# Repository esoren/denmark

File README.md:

This code is for an STM32F4-based amplifier controller board. More info is available on my website.

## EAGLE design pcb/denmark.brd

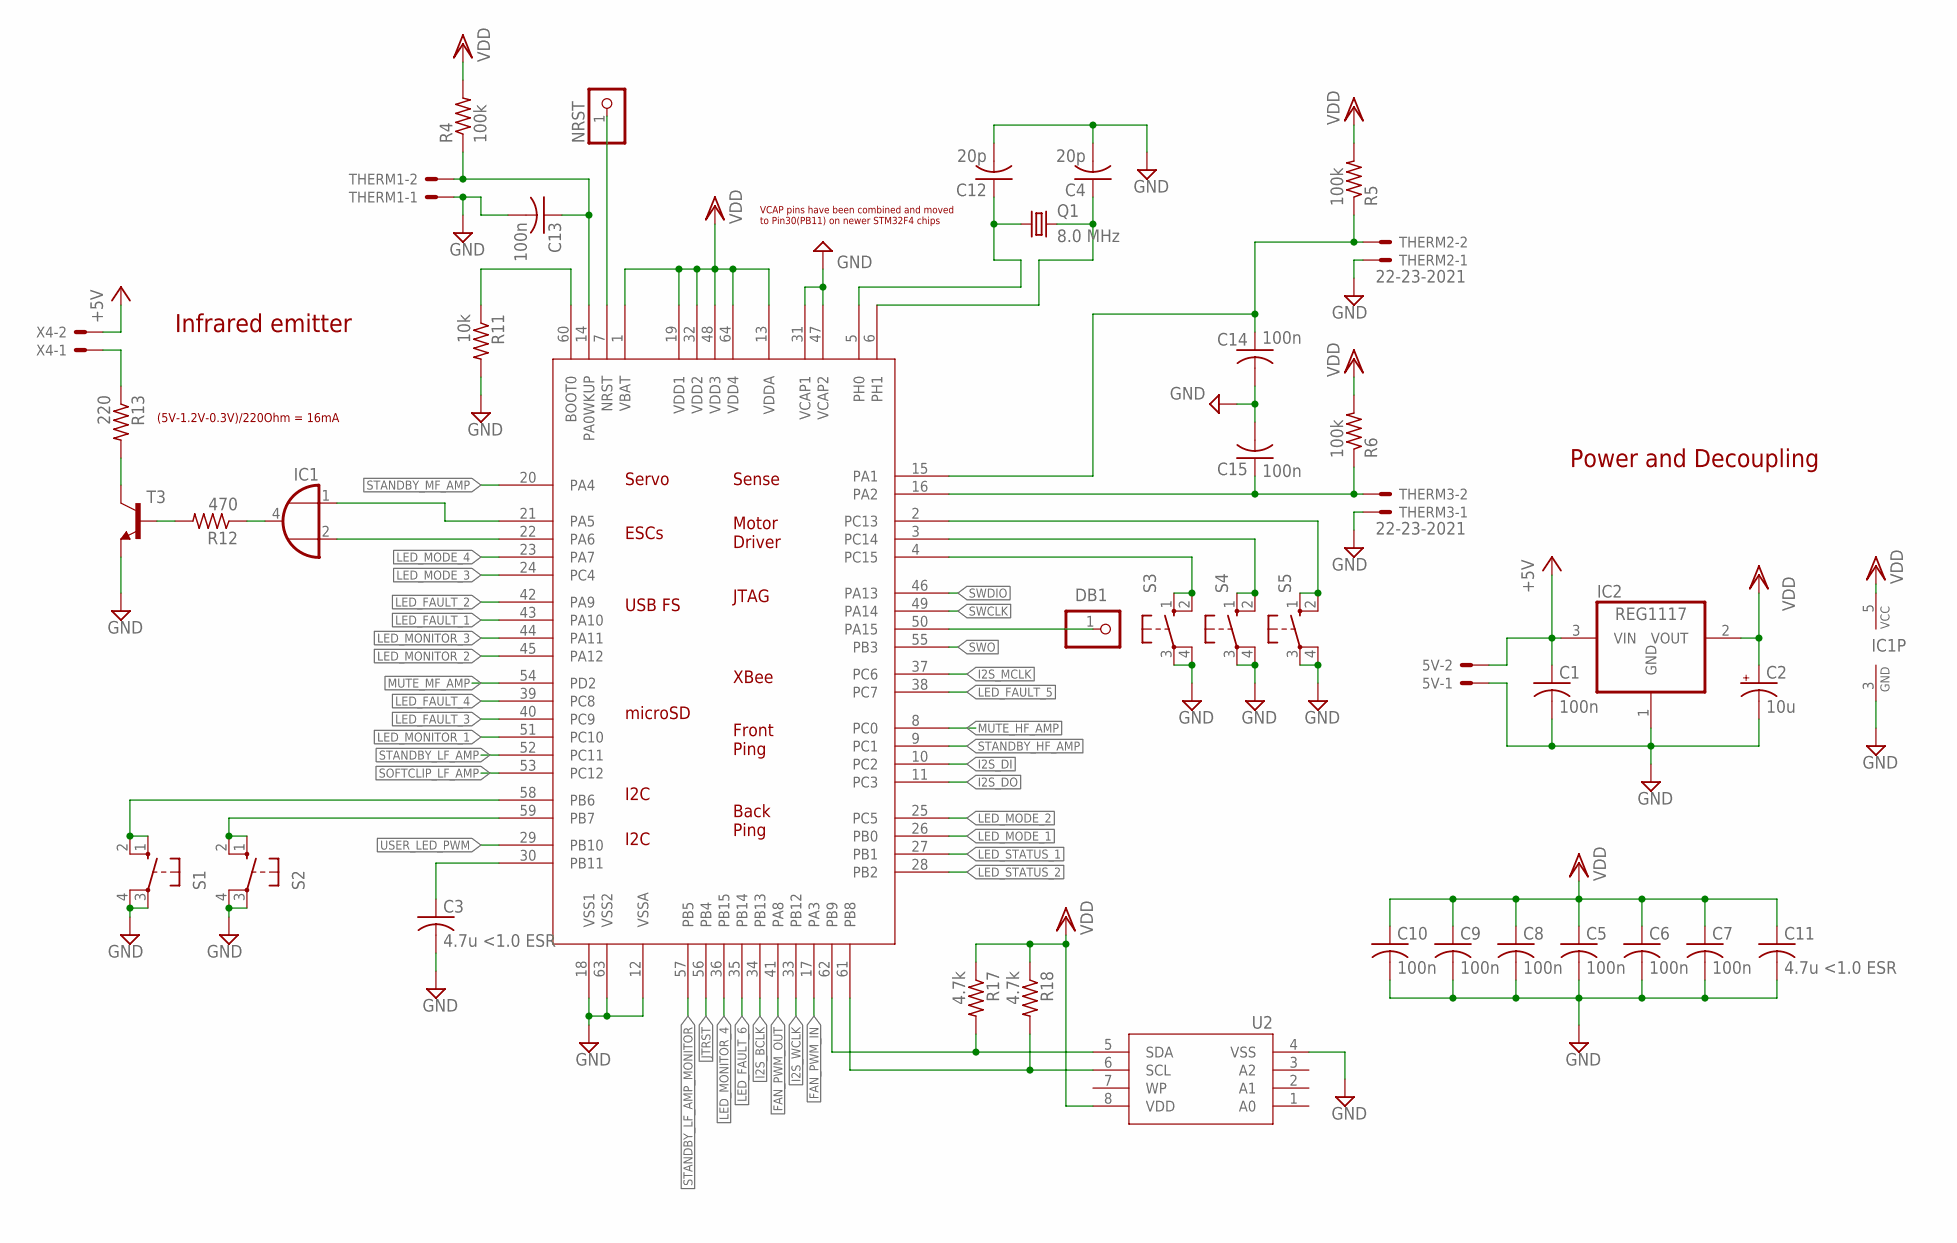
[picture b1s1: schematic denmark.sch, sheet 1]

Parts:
5V: 22-23-2021
C1: 100n; C0805
C2: 10u; E3,5-8
C3, C11: 4.7u <1.0 ESR; C1206
C4, C12: 20p; C0603K
C5, C6, C7, C8, C9, C10, C13, C14, C15: 100n; C0603K
DB1: PINHD-1X1; 1X01
IC1: 74AHC1G32DBV; SOT23-5
IC2: REG1117; SOT223
NRST: PINHD-1X1; 1X01
Q1: 8.0 MHz; HC49U-V
R4, R5, R6: 100k; R0603
R11: 10k; R0603
R12: 470; R0603
R13: 220; R0603
R17, R18: 4.7k; R0603
S1, S2, S3, S4, S5: 10-XX; B3F-10XX
T3: MMBT3904LT1-NPN-SOT23-BEC; SOT23-BEC
THERM1, THERM2, THERM3: 22-23-2021
U1: STM32F4_10X10_LQFP64; LQFP-ST-64-2
U2: MB85RCSOIC8; SOIC8
X4: 22-23-2021

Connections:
+5V: 5V.2, C1.1, IC2.3 (VIN), X4.2; also elsewhere on the board
BUTTON1_INPUT: S1.1 (S), S1.2 (S1), U1.58 (PB6)
BUTTON2_INPUT: S2.1 (S), S2.2 (S1), U1.59 (PB7)
BUTTON3_INPUT: S3.1 (S), S3.2 (S1), U1.4 (PC15)
BUTTON4_INPUT: S4.1 (S), S4.2 (S1), U1.3 (PC14)
BUTTON5_INPUT: S5.1 (S), S5.2 (S1), U1.2 (PC13)
FAN_PWM_IN: U1.17 (PA3); also elsewhere on the board
FAN_PWM_OUT: U1.41 (PA8); also elsewhere on the board
GND: 5V.1, C1.2, C2.-, C3.2, C4.2, C5.2, C6.2, C7.2, C8.2, C9.2, C10.2, C11.2, C12.2, C13.2, C14.2, C15.2, IC1.3 (GND), IC2.1 (GND), R11.2, S1.3, S1.4 (P1), S2.3, S2.4 (P1), S3.3, S3.4 (P1), S4.3, S4.4 (P1), S5.3, S5.4 (P1), T3.E, THERM1.1, THERM2.1, THERM3.1, U1.12 (VSSA), U1.18 (VSS1), U1.31 (VCAP1), U1.47 (VCAP2), U1.63 (VSS2), U2.4 (VSS); also elsewhere on the board
I2C_SCL: R18.2, U1.61 (PB8), U2.6 (SCL)
I2C_SDA: R17.2, U1.62 (PB9), U2.5 (SDA)
I2S_BCLK: U1.34 (PB13); also elsewhere on the board
I2S_DI: U1.10 (PC2); also elsewhere on the board
I2S_DO: U1.11 (PC3); also elsewhere on the board
I2S_MCLK: U1.37 (PC6); also elsewhere on the board
I2S_WCLK: U1.33 (PB12); also elsewhere on the board
IR_BASE: R12.2, T3.B
IR_CARRIER_OUT: IC1.2 (I1), U1.22 (PA6)
IR_COLLECTOR: R13.2, T3.C
IR_SIGNAL_OUT: IC1.1 (I0), U1.21 (PA5)
JTRST: U1.56 (PB4); also elsewhere on the board
LED_FAULT_1: U1.43 (PA10); also elsewhere on the board
LED_FAULT_2: U1.42 (PA9); also elsewhere on the board
LED_FAULT_3: U1.40 (PC9); also elsewhere on the board
LED_FAULT_4: U1.39 (PC8); also elsewhere on the board
LED_FAULT_5: U1.38 (PC7); also elsewhere on the board
LED_FAULT_6: U1.35 (PB14); also elsewhere on the board
LED_MODE_1: U1.26 (PB0); also elsewhere on the board
LED_MODE_2: U1.25 (PC5); also elsewhere on the board
LED_MODE_3: U1.24 (PC4); also elsewhere on the board
LED_MODE_4: U1.23 (PA7); also elsewhere on the board
LED_MONITOR_1: U1.51 (PC10); also elsewhere on the board
LED_MONITOR_2: U1.45 (PA12); also elsewhere on the board
LED_MONITOR_3: U1.44 (PA11); also elsewhere on the board
LED_MONITOR_4: U1.36 (PB15); also elsewhere on the board
LED_STATUS_1: U1.27 (PB1); also elsewhere on the board
LED_STATUS_2: U1.28 (PB2); also elsewhere on the board
MUTE_HF_AMP: U1.8 (PC0); also elsewhere on the board
MUTE_MF_AMP: U1.54 (PD2); also elsewhere on the board
unnamed: C3.1, U1.30 (PB11)
unnamed: DB1.1, U1.50 (PA15)
unnamed: R11.1, U1.60 (BOOT0)
unnamed: NRST.1, U1.7 (NRST)
unnamed: IC1.4 (O), R12.1
unnamed: R13.1, X4.1
RCC_OSC_IN: C12.1, Q1.1, U1.5 (PH0)
RCC_OSC_OUT: C4.1, Q1.2, U1.6 (PH1)
SOFTCLIP_LF_AMP: U1.53 (PC12); also elsewhere on the board
STANDBY_HF_AMP: U1.9 (PC1); also elsewhere on the board
STANDBY_LF_AMP: U1.52 (PC11); also elsewhere on the board
STANDBY_LF_AMP_MONITOR: U1.57 (PB5); also elsewhere on the board
STANDBY_MF_AMP: U1.20 (PA4); also elsewhere on the board
SWCLK: U1.49 (PA14); also elsewhere on the board
SWDIO: U1.46 (PA13); also elsewhere on the board
SWO: U1.55 (PB3); also elsewhere on the board
THERM1_ANALOG_INPUT: C13.1, R4.1, THERM1.2, U1.14 (PA0WKUP)
THERM2_ANALOG_INPUT: C14.1, R5.1, THERM2.2, U1.15 (PA1)
THERM3_ANALOG_INPUT: C15.1, R6.1, THERM3.2, U1.16 (PA2)
USER_LED_PWM: U1.29 (PB10); also elsewhere on the board
VDD: C2.+, C5.1, C6.1, C7.1, C8.1, C9.1, C10.1, C11.1, IC1.5 (VCC), IC2.2 (VOUT), R4.2, R5.2, R6.2, R17.1, R18.1, U1.1 (VBAT), U1.13 (VDDA), U1.19 (VDD1), U1.32 (VDD2), U1.48 (VDD3), U1.64 (VDD4), U2.8 (VDD); also elsewhere on the board

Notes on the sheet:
Power and Decoupling
(5V-1.2V-0.3V)/220Ohm = 16mA
Infrared emitter
VCAP pins have been combined and moved to Pin30(PB11) on newer STM32F4 chips

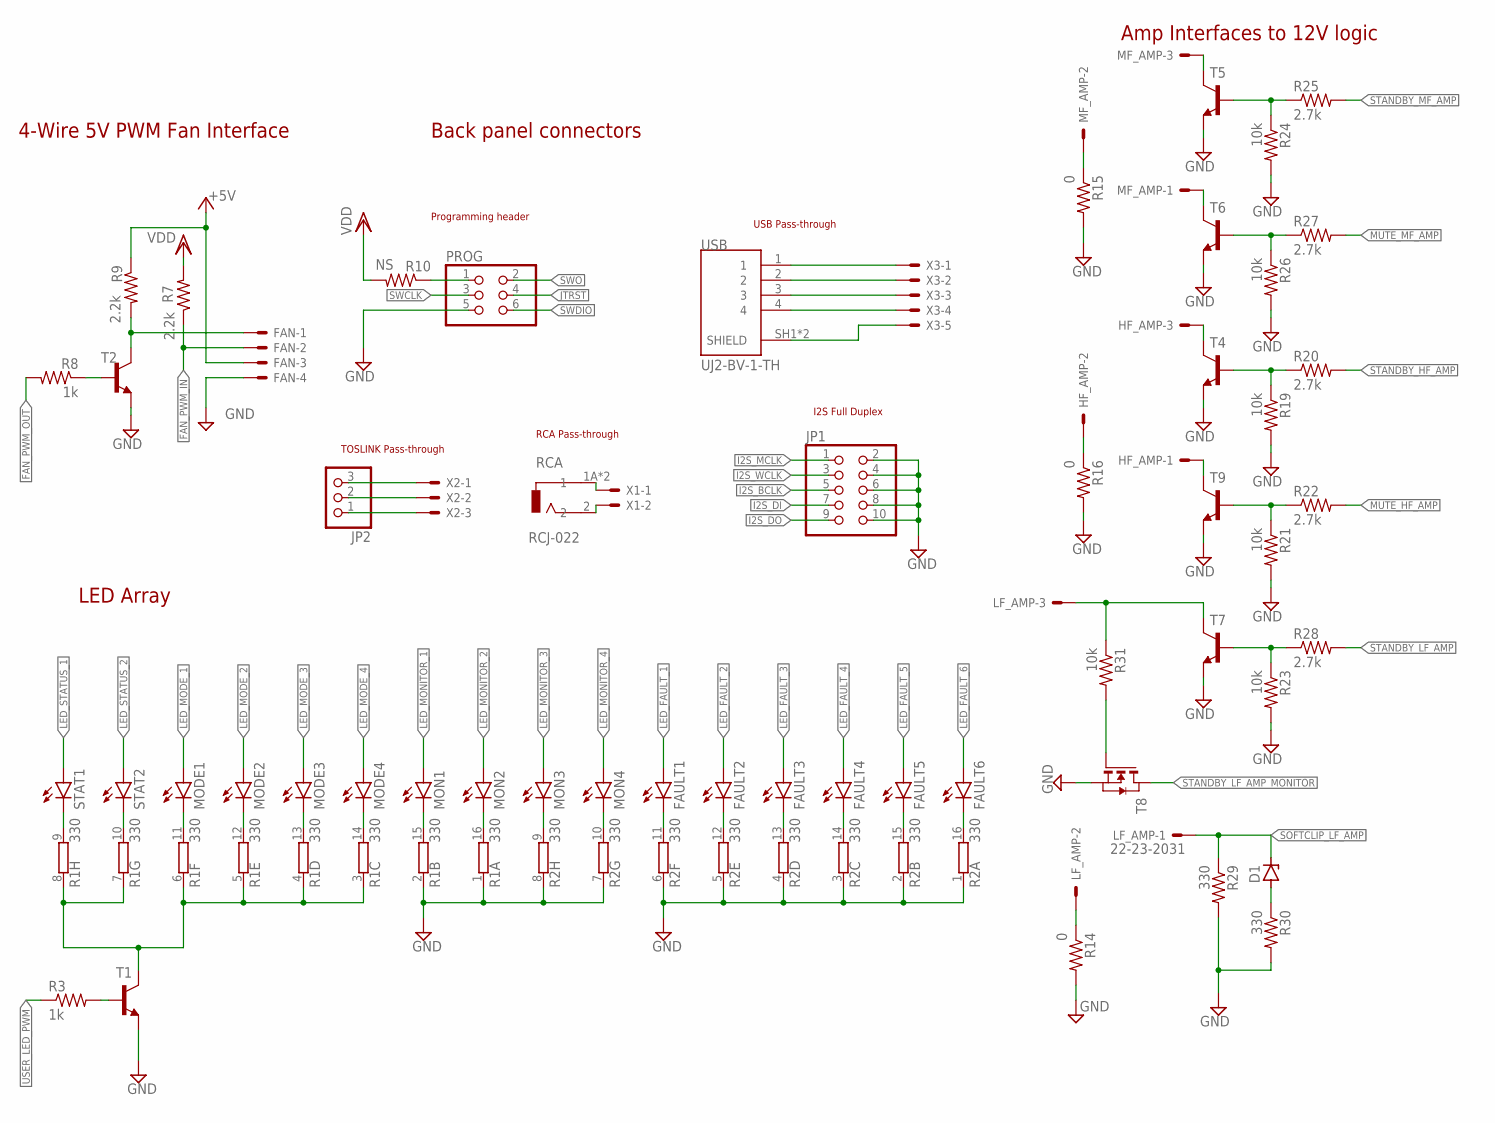
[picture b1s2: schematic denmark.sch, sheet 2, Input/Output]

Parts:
D1: ZENER-DIODESOD80C; SOD80C
FAN: 22-23-2041
FAULT1, FAULT2, FAULT3, FAULT4, FAULT5, FAULT6: LEDCHIPLED_0805; CHIPLED_0805
HF_AMP: 22-23-2031
JP1: PINHD-2X5; 2X05
JP2: PINHD-1X3; 1X03
LF_AMP: 22-23-2031
MF_AMP: 22-23-2031
MODE1, MODE2, MODE3, MODE4: LEDCHIPLED_0805; CHIPLED_0805
MON1, MON2, MON3, MON4: LEDCHIPLED_0805; CHIPLED_0805
PROG: PINHD-2X3; 2X03
R1, R2: 330; SO16
R3, R8: 1k; R0603
R7, R9: 2.2k; R0603
R10: NS; R0603
R14, R15, R16: 0; R0603
R19, R21, R23, R24, R26, R31: 10k; R0603
R20, R22, R25, R27, R28: 2.7k; R0603
R29, R30: 330; R0603
RCA: RCJ-022; CUI_RCJ-022
STAT1, STAT2: LEDCHIPLED_0805; CHIPLED_0805
T1, T2, T4, T5, T6, T7, T9: MMBT3904LT1-NPN-SOT23-BEC; SOT23-BEC
T8: NMOSSOT23; SOT-23
USB: UJ2-BV-1-TH; CUI_UJ2-BV-1-TH
X1: 22-23-2021
X2: 22-23-2031
X3: 22-23-2051

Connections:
+5V: FAN.3, R9.1; also elsewhere on the board
FAN_PWM_IN: FAN.2, R7.1; also elsewhere on the board
FAN_PWM_OUT: R8.2; also elsewhere on the board
GND: FAN.4, JP1.2, JP1.4, JP1.6, JP1.8, JP1.10, PROG.5, R1.1, R1.2 (1), R2.1, R2.2 (1), R2.3 (1), R2.4 (1), R2.5 (1), R2.6 (1), R2.7 (1), R2.8 (1), R14.2, R15.2, R16.2, R19.2, R21.2, R23.2, R24.2, R26.2, R29.2, R30.2, T1.E, T2.E, T4.E, T5.E, T6.E, T7.E, T8.2 (S), T9.E; also elsewhere on the board
I2S_BCLK: JP1.5; also elsewhere on the board
I2S_DI: JP1.7; also elsewhere on the board
I2S_DO: JP1.9; also elsewhere on the board
I2S_MCLK: JP1.1; also elsewhere on the board
I2S_WCLK: JP1.3; also elsewhere on the board
JTRST: PROG.4; also elsewhere on the board
LED_FAULT_1: FAULT1.A; also elsewhere on the board
LED_FAULT_2: FAULT2.A; also elsewhere on the board
LED_FAULT_3: FAULT3.A; also elsewhere on the board
LED_FAULT_4: FAULT4.A; also elsewhere on the board
LED_FAULT_5: FAULT5.A; also elsewhere on the board
LED_FAULT_6: FAULT6.A; also elsewhere on the board
LED_MODE_1: MODE1.A; also elsewhere on the board
LED_MODE_2: MODE2.A; also elsewhere on the board
LED_MODE_3: MODE3.A; also elsewhere on the board
LED_MODE_4: MODE4.A; also elsewhere on the board
LED_MONITOR_1: MON1.A; also elsewhere on the board
LED_MONITOR_2: MON2.A; also elsewhere on the board
LED_MONITOR_3: MON3.A; also elsewhere on the board
LED_MONITOR_4: MON4.A; also elsewhere on the board
LED_STATUS_1: STAT1.A; also elsewhere on the board
LED_STATUS_2: STAT2.A; also elsewhere on the board
LED_USER_ANODE: R1.3 (1), R1.4 (1), R1.5 (1), R1.6 (1), R1.7 (1), R1.8 (1), T1.C
MUTE_HF_AMP: R22.2; also elsewhere on the board
MUTE_MF_AMP: R27.2; also elsewhere on the board
unnamed: R1.9 (2), STAT1.C
unnamed: R1.10 (2), STAT2.C
unnamed: MODE1.C, R1.11 (2)
unnamed: MODE2.C, R1.12 (2)
unnamed: MODE3.C, R1.13 (2)
unnamed: MODE4.C, R1.14 (2)
unnamed: MON1.C, R1.15 (2)
unnamed: MON2.C, R1.16 (2)
unnamed: MON3.C, R2.9 (2)
unnamed: MON4.C, R2.10 (2)
unnamed: FAULT1.C, R2.11 (2)
unnamed: FAULT2.C, R2.12 (2)
unnamed: FAULT3.C, R2.13 (2)
unnamed: FAULT4.C, R2.14 (2)
unnamed: FAULT5.C, R2.15 (2)
unnamed: FAULT6.C, R2.16 (2)
unnamed: R3.2, T1.B
unnamed: HF_AMP.3, T4.C
unnamed: R19.1, R20.1, T4.B
unnamed: HF_AMP.1, T9.C
unnamed: R21.1, R22.1, T9.B
unnamed: LF_AMP.3, R31.1, T7.C
unnamed: MF_AMP.3, T5.C
unnamed: R24.1, R25.1, T5.B
unnamed: FAN.1, R9.2, T2.C
unnamed: R8.1, T2.B
unnamed: MF_AMP.1, T6.C
unnamed: R26.1, R27.1, T6.B
unnamed: R23.1, R28.1, T7.B
unnamed: RCA.1A (1), RCA.1B (1), X1.1
unnamed: RCA.2, X1.2
unnamed: JP2.3, X2.1
unnamed: JP2.2, X2.2
unnamed: JP2.1, X2.3
unnamed: R31.2, T8.3 (G)
unnamed: USB.1, X3.1
unnamed: USB.2, X3.2
unnamed: USB.3, X3.3
unnamed: USB.4, X3.4
unnamed: USB.SH1 (SHIELD), USB.SH2 (SHIELD), X3.5
unnamed: D1.A, R30.1
unnamed: LF_AMP.2, R14.1
unnamed: MF_AMP.2, R15.1
unnamed: HF_AMP.2, R16.1
SOFTCLIP_LF_AMP: D1.C, LF_AMP.1, R29.1; also elsewhere on the board
STANDBY_HF_AMP: R20.2; also elsewhere on the board
STANDBY_LF_AMP: R28.2; also elsewhere on the board
STANDBY_LF_AMP_MONITOR: T8.1 (D); also elsewhere on the board
STANDBY_MF_AMP: R25.2; also elsewhere on the board
ST_VDD: PROG.1, R10.1
SWCLK: PROG.3; also elsewhere on the board
SWDIO: PROG.6; also elsewhere on the board
SWO: PROG.2; also elsewhere on the board
USER_LED_PWM: R3.1; also elsewhere on the board
VDD: R7.2, R10.2; also elsewhere on the board

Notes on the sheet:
Back panel connectors
LED Array
TOSLINK Pass-through
I2S Full Duplex
USB Pass-through
Programming header
RCA Pass-through
Amp Interfaces to 12V logic
4-Wire 5V PWM Fan Interface

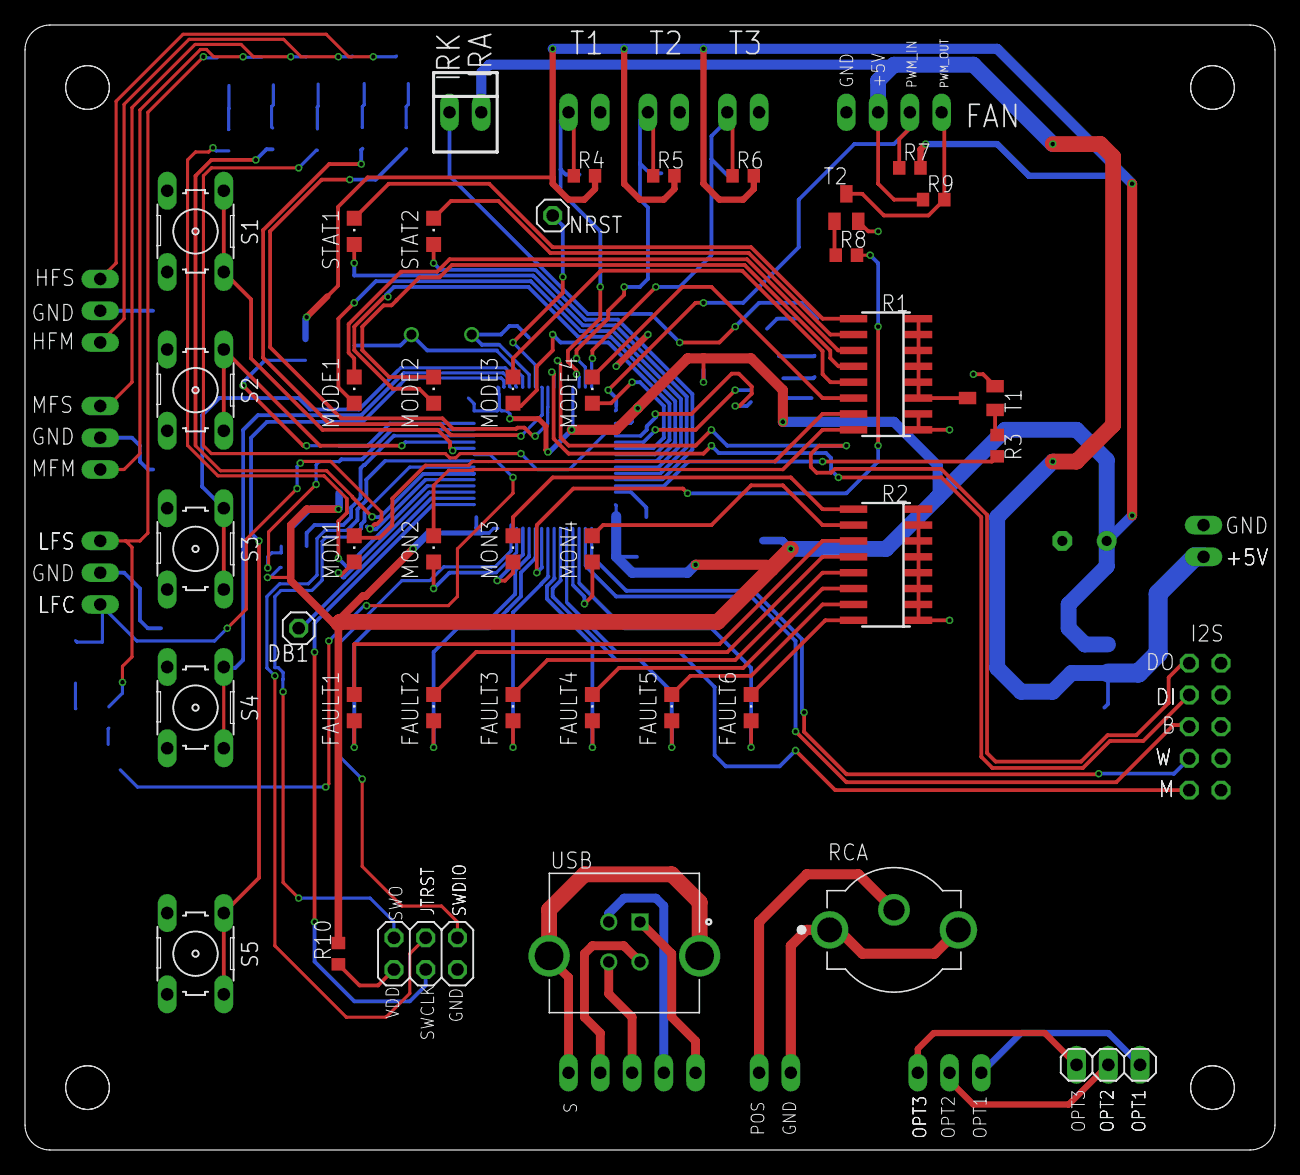
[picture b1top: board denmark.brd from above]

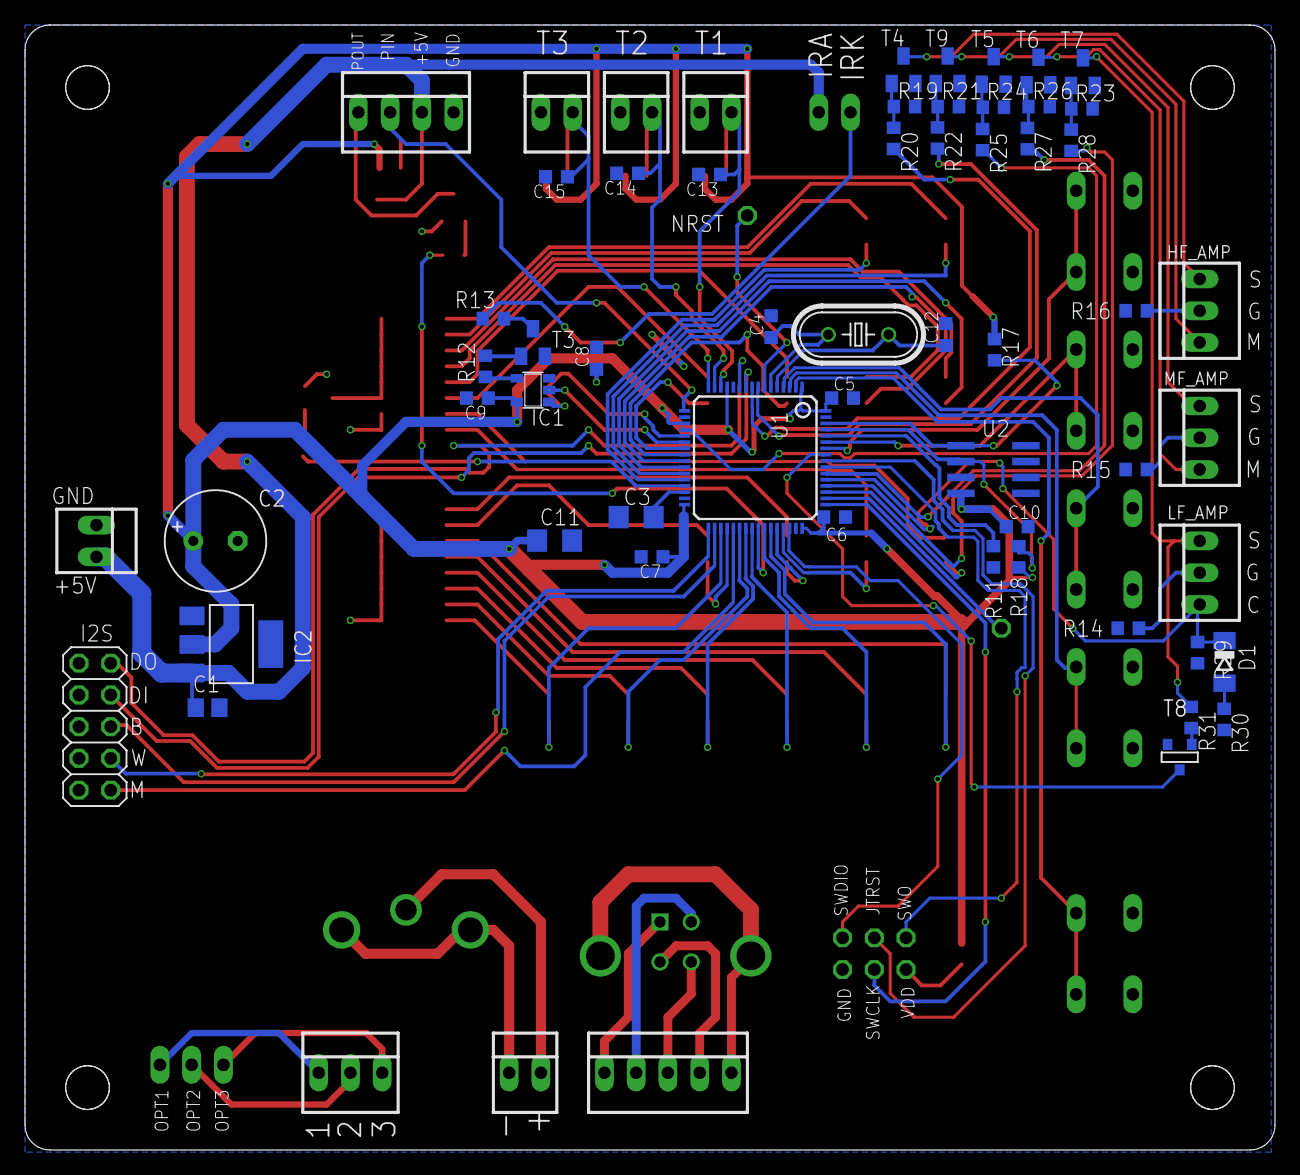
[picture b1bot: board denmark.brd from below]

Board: 2 copper layers, 100.0 x 90.0 mm, 101 parts (61 on the bottom side), 106 nets.

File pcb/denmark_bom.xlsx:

Digikey P/N | QTY | Reference | Doubled | Description
399-C0603C104K8RAC7867CT-ND | 10 | C1 C5 C6 C7 C8 C9 C10 C13 C14 C15 | 20 | 100nf 0603 capacitor
587-GMK316AB7475MLHTCT-ND | 2 | C3 C11 | 4 | 4.7uF 1206 low ESR
1189-1513-1-ND | 1 | C2 | 2 | 10uF 8mm cap
475-1410-1-ND | 6 | MODE1 MODE2 MODE3 MODE4 STAT1 STAT2 | 12 | green 0805 led
732-4987-1-ND | 4 | MON1 MON2 MON3 MON4 | 8 | yellow 0805 led
475-1278-1-ND | 6 | FAULT1 FAULT2 FAULT3 FAULT4 FAULT5 FAULT6 | 12 | red 0805 led
497-STM32F401RET7-ND | 1 | U1 | 2 | stm32f4 mcu
RNCP0603FTD1K00CT-ND | 4 | R3 R8 | 8 | 1k 0603 resistor
311-100KHRCT-ND | 3 | R4 R5 R6 | 6 | 100k 0603 resistor
311-2.20KHRCT-ND | 2 | R7 R9 | 4 | 2.2k 0603 resistor
RMCF0201FT10K0CT-ND | 7 | R11 R19 R21 R23 R24 R26 R31 | 14 | 10k 0603 resistor
311-4.7KGRCT-ND | 2 | R17 R18 | 4 | 4.7k 0603 resistor
RMCF0603ZT0R00CT-ND | 3 | R14 R15 R16 | 6 | 0 0603 resistor
VSSR16-330-JI-ND | 2 | R1 R2 | 4 | resistor network - 330
865-1261-1-ND | 1 | U2 | 2 | FRAM
497-1242-1-ND | 1 | IC2 | 2 | 1117 LDO
XC1922-ND | 1 | Q1 | 2 | 8.0 MHz Crystal
CP-1408-ND | 1 | RCA | 2 | RCA connector
102-4000-ND | 1 | USB | 2 | USB connector
296-SN74AHC1G08DBV3CT-ND | 1 | IC1 | 2 | AND Gate
SW400-ND | 5 | S1 S2 S3 S4 S5 | 10 | tactile switch
A98333-ND | 6 | 5V THERM1 THERM2 THERM3 X1 X4 | 12 | 2 pin terminal block 0.1"
A98334-ND | 4 | X2 LF_AMP MF_AMP HF_AMP | 8 | 3 pin terminal block 0.1":
A98335-ND | 1 | FAN | 2 | 4 pin terminal block 0.1"
A98336-ND | 1 | X3 | 2 | 5 pin terminal block 0.1"
MMBT3904LT1HTSA1CT-ND | 7 | T1 T2 T3 T5 T6 T7 T9 | 14 | npn transistor sot23
1276-1187-1-ND | 2 | C4 C12 | 4 | 20p 0603 capacitor
CR0603-JW-331ELFCT-ND | 2 | R29 R30 | 4 | 330 0603 resistor
118-CR0603-JW-221ELFCT-ND | 1 | R12 | 2 | 220 0603 resistor
CR0603-JW-471ELFCT-ND | 1 | R13 | 2 | 470 0603 resistor
2N7002-FDICT-ND | 1 | T8 | 2 | NMOS switch
1727-2097-1-ND | 1 | D1 | 2 | 3v3 zener diode

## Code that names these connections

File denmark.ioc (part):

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Mcu.Name=STM32F401R(D-E)Tx
Mcu.Package=LQFP64
Mcu.UserName=STM32F401RETx
PA0-WKUP.GPIOParameters=GPIO_Label
PA0-WKUP.GPIO_Label=THERM1_ANALOG_INPUT
PA0-WKUP.Signal=ADCx_IN0
PA1.GPIOParameters=GPIO_Label
PA1.GPIO_Label=THERM2_ANALOG_INPUT
PA1.Signal=ADCx_IN1
PA10.GPIOParameters=GPIO_Label
PA10.GPIO_Label=LED_FAULT_1
PA10.Signal=GPIO_Output
PA11.GPIOParameters=GPIO_Label
PA11.GPIO_Label=LED_MONITOR_3
PA11.Signal=GPIO_Output
PA12.GPIOParameters=GPIO_Label
PA12.GPIO_Label=LED_MONITOR_2
PA12.Signal=GPIO_Output
PA13.Mode=JTAG_5_pins
PA13.Signal=SYS_JTMS-SWDIO
PA14.Mode=JTAG_5_pins
PA14.Signal=SYS_JTCK-SWCLK
PA15.Mode=JTAG_5_pins
PA15.Signal=SYS_JTDI
PA2.GPIOParameters=GPIO_Label
PA2.GPIO_Label=THERM3_ANALOG_INPUT
PA2.Signal=ADCx_IN2
PA3.Signal=S_TIM5_CH4
PA4.GPIOParameters=PinState,GPIO_Label
PA4.GPIO_Label=STANDBY_MF_AMP
PA4.PinState=GPIO_PIN_SET
PA4.Signal=GPIO_Output
PA5.GPIOParameters=GPIO_Label
PA5.GPIO_Label=IR_SIGNAL_OUT
PA5.Signal=GPIO_Output
PA6.GPIOParameters=GPIO_Label
PA6.GPIO_Label=IR_CARRIER_OUT
PA6.Signal=S_TIM3_CH1
PA7.GPIOParameters=GPIO_Label
PA7.GPIO_Label=LED_MODE_4
PA7.Signal=GPIO_Output
PA8.GPIOParameters=GPIO_Speed,GPIO_Label
PA8.GPIO_Label=FAN_PWM
PA8.GPIO_Speed=GPIO_SPEED_FREQ_HIGH
PA8.Signal=S_TIM1_CH1
PA9.GPIOParameters=GPIO_Label
PA9.GPIO_Label=LED_FAULT_2
PA9.Signal=GPIO_Output
PB0.GPIOParameters=GPIO_Label
PB0.GPIO_Label=LED_MODE_1
PB0.Signal=GPIO_Output
PB1.GPIOParameters=GPIO_Label
PB1.GPIO_Label=LED_STATUS_1
PB1.Signal=GPIO_Output
PB10.GPIOParameters=GPIO_Label
PB10.GPIO_Label=USER_LED_PWM
PB10.Signal=S_TIM2_CH3
PB14.GPIOParameters=GPIO_Label
PB14.GPIO_Label=LED_FAULT_6
PB14.Signal=GPIO_Output
PB15.GPIOParameters=GPIO_Label
PB15.GPIO_Label=LED_MONITOR_4
PB15.Signal=GPIO_Output
PB2.GPIOParameters=GPIO_Label
PB2.GPIO_Label=LED_STATUS_2
PB2.Signal=GPIO_Output
PB3.Mode=JTAG_5_pins
PB3.Signal=SYS_JTDO-SWO
PB4.Mode=JTAG_5_pins
PB4.Signal=SYS_JTRST
PB6.GPIOParameters=GPIO_PuPd,GPIO_Label
PB6.GPIO_Label=BUTTON1_INPUT
PB6.GPIO_PuPd=GPIO_PULLUP
PB6.Signal=GPIO_Input
PB7.GPIOParameters=GPIO_PuPd,GPIO_Label
PB7.GPIO_Label=BUTTON2_INPUT
PB7.GPIO_PuPd=GPIO_PULLUP
PB7.Signal=GPIO_Input
PB8.GPIOParameters=GPIO_Label
PB8.GPIO_Label=I2C_SCL
PB8.Mode=I2C
PB8.Signal=I2C1_SCL
PB9.GPIOParameters=GPIO_Label
PB9.GPIO_Label=I2C_SDA
PB9.Mode=I2C
PB9.Signal=I2C1_SDA
PC0.GPIOParameters=PinState,GPIO_Label
PC0.GPIO_Label=MUTE_HF_AMP
PC0.PinState=GPIO_PIN_SET
PC0.Signal=GPIO_Output
PC1.GPIOParameters=PinState,GPIO_Label
PC1.GPIO_Label=STANDBY_HF_AMP
PC1.PinState=GPIO_PIN_SET
PC1.Signal=GPIO_Output
PC10.GPIOParameters=GPIO_Label
PC10.GPIO_Label=LED_MONITOR_1
PC10.Signal=GPIO_Output
PC11.GPIOParameters=PinState,GPIO_PuPd,GPIO_Label,GPIO_ModeDefaultOutputPP
PC11.GPIO_Label=STANDBY_LF_AMP_OUTPUT
PC11.GPIO_ModeDefaultOutputPP=GPIO_MODE_OUTPUT_PP
PC11.GPIO_PuPd=GPIO_NOPULL
PC11.PinState=GPIO_PIN_SET
PC11.Signal=GPIO_Output
PC12.GPIOParameters=GPIO_PuPd,GPIO_Label
PC12.GPIO_Label=SOFTCLIP_LF_AMP_INPUT
PC12.GPIO_PuPd=GPIO_PULLUP
PC12.Signal=GPIO_Input
PC13-ANTI_TAMP.GPIOParameters=GPIO_PuPd,GPIO_Label
PC13-ANTI_TAMP.GPIO_Label=BUTTON5_INPUT
PC13-ANTI_TAMP.GPIO_PuPd=GPIO_PULLUP
PC13-ANTI_TAMP.Signal=GPIO_Input
PC14-OSC32_IN.GPIOParameters=GPIO_PuPd,GPIO_Label
PC14-OSC32_IN.GPIO_Label=BUTTON4_INPUT
PC14-OSC32_IN.GPIO_PuPd=GPIO_PULLUP
PC14-OSC32_IN.Signal=GPIO_Input
PC15-OSC32_OUT.GPIOParameters=GPIO_PuPd,GPIO_Label
PC15-OSC32_OUT.GPIO_Label=BUTTON3_INPUT
PC15-OSC32_OUT.GPIO_PuPd=GPIO_PULLUP
PC15-OSC32_OUT.Signal=GPIO_Input
PC3.GPIOParameters=GPIO_PuPd,GPIO_Label
PC3.GPIO_Label=STANDBY_PROTECT_LF_INPUT
PC3.GPIO_PuPd=GPIO_PULLUP
PC3.Signal=GPIO_Input
PC4.GPIOParameters=GPIO_Label
PC4.GPIO_Label=LED_MODE_3
PC4.Signal=GPIO_Output
PC5.GPIOParameters=GPIO_Label
PC5.GPIO_Label=LED_MODE_2
PC5.Signal=GPIO_Output
PC6.GPIOParameters=GPIO_PuPd,GPIO_Label
PC6.GPIO_Label=GENERAL_INPUT_1
PC6.GPIO_PuPd=GPIO_PULLUP
PC6.Signal=GPIO_Input
PC7.GPIOParameters=GPIO_Label
PC7.GPIO_Label=LED_FAULT_5
PC7.Signal=GPIO_Output
PC8.GPIOParameters=GPIO_Label
PC8.GPIO_Label=LED_FAULT_4
PC8.Signal=GPIO_Output
PC9.GPIOParameters=GPIO_Label
PC9.GPIO_Label=LED_FAULT_3
PC9.Signal=GPIO_Output
PD2.GPIOParameters=PinState,GPIO_Label
PD2.GPIO_Label=MUTE_MF_AMP
PD2.PinState=GPIO_PIN_SET
PD2.Signal=GPIO_Output
PH0\ -\ OSC_IN.Mode=HSE-External-Oscillator
PH0\ -\ OSC_IN.Signal=RCC_OSC_IN
PH1\ -\ OSC_OUT.Mode=HSE-External-Oscillator
PH1\ -\ OSC_OUT.Signal=RCC_OSC_OUT
RCC.HSE_VALUE=8000000
RCC.SYSCLKFreq_VALUE=84000000
RCC.SYSCLKSource=RCC_SYSCLKSOURCE_PLLCLK
board=custom

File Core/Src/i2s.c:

/* USER CODE BEGIN Header */
/**
  ******************************************************************************
  * @file    i2s.c
  * @brief   This file provides code for the configuration
  *          of the I2S instances.
  ******************************************************************************
  * @attention
  *
  * Copyright (c) 2023 STMicroelectronics.
  * All rights reserved.
  *
  * This software is licensed under terms that can be found in the LICENSE file
  * in the root directory of this software component.
  * If no LICENSE file comes with this software, it is provided AS-IS.
  *
  ******************************************************************************
  */
/* USER CODE END Header */
/* Includes ------------------------------------------------------------------*/
#include "i2s.h"

/* USER CODE BEGIN 0 */

/* USER CODE END 0 */

I2S_HandleTypeDef hi2s2;

/* I2S2 init function */
void MX_I2S2_Init(void)
{

  /* USER CODE BEGIN I2S2_Init 0 */

  /* USER CODE END I2S2_Init 0 */

  /* USER CODE BEGIN I2S2_Init 1 */

  /* USER CODE END I2S2_Init 1 */
  hi2s2.Instance = SPI2;
  hi2s2.Init.Mode = I2S_MODE_MASTER_TX;
  hi2s2.Init.Standard = I2S_STANDARD_PHILIPS;
  hi2s2.Init.DataFormat = I2S_DATAFORMAT_16B;
  hi2s2.Init.MCLKOutput = I2S_MCLKOUTPUT_ENABLE;
  hi2s2.Init.AudioFreq = I2S_AUDIOFREQ_8K;
  hi2s2.Init.CPOL = I2S_CPOL_LOW;
  hi2s2.Init.ClockSource = I2S_CLOCK_PLL;
  hi2s2.Init.FullDuplexMode = I2S_FULLDUPLEXMODE_ENABLE;
  if (HAL_I2S_Init(&hi2s2) != HAL_OK)
  {
    Error_Handler();
  }
  /* USER CODE BEGIN I2S2_Init 2 */

  /* USER CODE END I2S2_Init 2 */

}

void HAL_I2S_MspInit(I2S_HandleTypeDef* i2sHandle)
{

  GPIO_InitTypeDef GPIO_InitStruct = {0};
  RCC_PeriphCLKInitTypeDef PeriphClkInitStruct = {0};
  if(i2sHandle->Instance==SPI2)
  {
  /* USER CODE BEGIN SPI2_MspInit 0 */

  /* USER CODE END SPI2_MspInit 0 */

  /** Initializes the peripherals clock
  */
    PeriphClkInitStruct.PeriphClockSelection = RCC_PERIPHCLK_I2S;
    PeriphClkInitStruct.PLLI2S.PLLI2SN = 50;
    PeriphClkInitStruct.PLLI2S.PLLI2SR = 2;
    if (HAL_RCCEx_PeriphCLKConfig(&PeriphClkInitStruct) != HAL_OK)
    {
      Error_Handler();
    }

    /* I2S2 clock enable */
    __HAL_RCC_SPI2_CLK_ENABLE();

    __HAL_RCC_GPIOC_CLK_ENABLE();
    __HAL_RCC_GPIOB_CLK_ENABLE();
    /**I2S2 GPIO Configuration
    PC2     ------> I2S2_ext_SD
    PC3     ------> I2S2_SD
    PB12     ------> I2S2_WS
    PB13     ------> I2S2_CK
    PC6     ------> I2S2_MCK
    */
    GPIO_InitStruct.Pin = I2S_DI_Pin;
    GPIO_InitStruct.Mode = GPIO_MODE_AF_PP;
    GPIO_InitStruct.Pull = GPIO_NOPULL;
    GPIO_InitStruct.Speed = GPIO_SPEED_FREQ_LOW;
    GPIO_InitStruct.Alternate = GPIO_AF6_I2S2ext;
    HAL_GPIO_Init(I2S_DI_GPIO_Port, &GPIO_InitStruct);

    GPIO_InitStruct.Pin = I2S_DO_Pin|I2S_MCLK_Pin;
    GPIO_InitStruct.Mode = GPIO_MODE_AF_PP;
    GPIO_InitStruct.Pull = GPIO_NOPULL;
    GPIO_InitStruct.Speed = GPIO_SPEED_FREQ_LOW;
    GPIO_InitStruct.Alternate = GPIO_AF5_SPI2;
    HAL_GPIO_Init(GPIOC, &GPIO_InitStruct);

    GPIO_InitStruct.Pin = I2S_WCLK_Pin|I2S_BCLK_Pin;
    GPIO_InitStruct.Mode = GPIO_MODE_AF_PP;
    GPIO_InitStruct.Pull = GPIO_NOPULL;
    GPIO_InitStruct.Speed = GPIO_SPEED_FREQ_LOW;
    GPIO_InitStruct.Alternate = GPIO_AF5_SPI2;
    HAL_GPIO_Init(GPIOB, &GPIO_InitStruct);

  /* USER CODE BEGIN SPI2_MspInit 1 */

  /* USER CODE END SPI2_MspInit 1 */
  }
}

void HAL_I2S_MspDeInit(I2S_HandleTypeDef* i2sHandle)
{

  if(i2sHandle->Instance==SPI2)
  {
  /* USER CODE BEGIN SPI2_MspDeInit 0 */

  /* USER CODE END SPI2_MspDeInit 0 */
    /* Peripheral clock disable */
    __HAL_RCC_SPI2_CLK_DISABLE();

    /**I2S2 GPIO Configuration
    PC2     ------> I2S2_ext_SD
    PC3     ------> I2S2_SD
    PB12     ------> I2S2_WS
    PB13     ------> I2S2_CK
    PC6     ------> I2S2_MCK
    */
    HAL_GPIO_DeInit(GPIOC, I2S_DI_Pin|I2S_DO_Pin|I2S_MCLK_Pin);

    HAL_GPIO_DeInit(GPIOB, I2S_WCLK_Pin|I2S_BCLK_Pin);

  /* USER CODE BEGIN SPI2_MspDeInit 1 */

  /* USER CODE END SPI2_MspDeInit 1 */
  }
}

/* USER CODE BEGIN 1 */

/* USER CODE END 1 */

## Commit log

2023-03-03 Initial commit and start of display task
2023-03-05 Add test for display function.
2023-03-05 Update display task to use a bit mask instead of array
2023-03-05 Add states for indicator display masks and an input task
2023-03-05 Add internal pullups for button inputs
2023-03-05 Minor changes to display function
2023-03-05 Add DSP mode selection
2023-03-05 Add task for temperature measurement
2023-03-05 Add fault flags and temperature measurement
2023-03-06 Add fan control
2023-03-06 Add fan monitor and fault handling
2023-03-07 Add queue to start and stop temperature monitoring
2023-03-07 Add fan monitor on off control
2023-03-07 Add support for 0 RPM fan setting
2023-03-10 Add standby function and adjust pin settings for board rework
2023-03-10 Finish standby toggle and control functions
2023-03-11 Add fan speed messages. Standby turns off fan.
2023-03-11 Add fram read and write byte functions
2023-03-11 DSP state saves to and loads from FRAM
2023-03-11 Add infrared RC5 protocol
2023-03-14 Adjust boot sequence and timings against real hardware
2023-03-14 Restore previous state of amplifiers after loading DSP
2023-03-14 Clean up gitignore
2023-03-14 Adjust timings for smoother exit from Standby mode
2023-03-14 Add pcb board file and schematic
2023-03-14 Update MCU footprint and add BOM
2023-03-14 Update BOM and PCB to incorporate reworks
2023-03-14 Silkscreen cleanup
2023-03-15 Cleanup Schematic
2023-03-15 Update BOM to add 12V interface components
2023-03-16 Added SWV debug printf function and temperature tracing
2023-03-16 More BOM and schematic cleanup
